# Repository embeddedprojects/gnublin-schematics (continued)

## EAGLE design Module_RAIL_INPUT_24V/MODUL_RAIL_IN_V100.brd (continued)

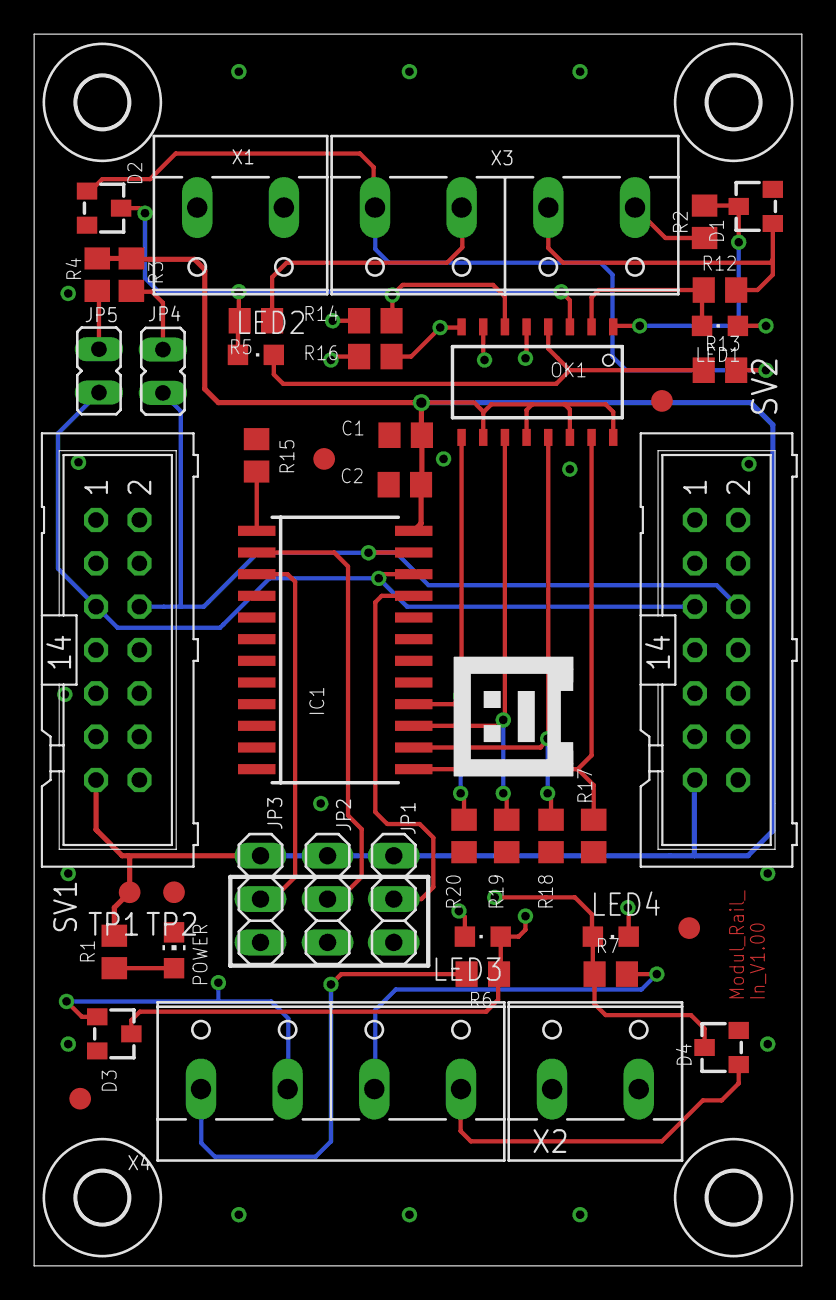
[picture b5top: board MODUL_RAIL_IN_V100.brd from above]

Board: 4 copper layers, 45.0 x 72.2 mm, 51 parts (0 on the bottom side), 41 nets.
